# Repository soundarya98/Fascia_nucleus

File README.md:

# Fascia_nucleus
files related to the Fascia project

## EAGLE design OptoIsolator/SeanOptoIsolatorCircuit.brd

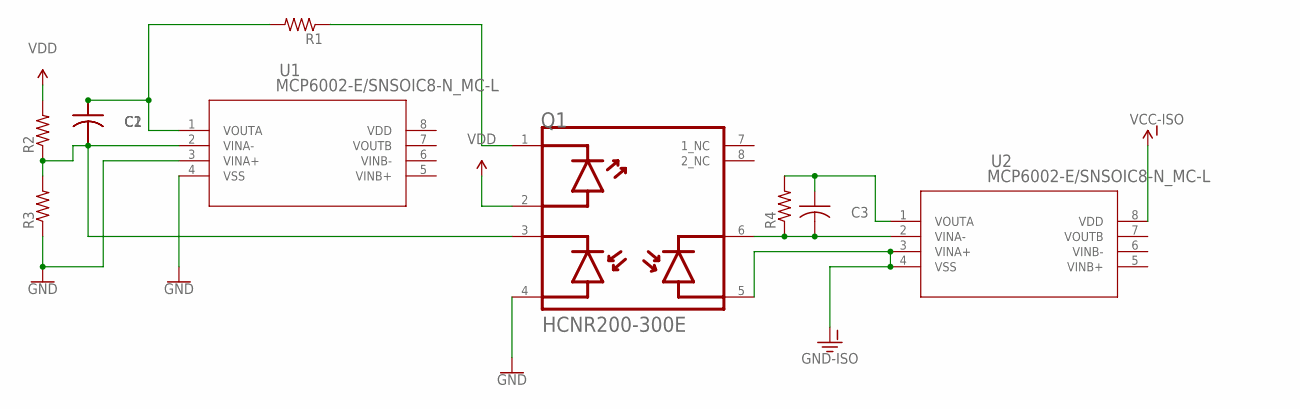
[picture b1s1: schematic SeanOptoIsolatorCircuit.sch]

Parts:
C1, C2, C3: C-US025-024X044; C025-024X044
Q1: BROADCOM_HCNR200-300EBROADCOM_HCNR200-300E_0_0; BROADCOM_HCNR200-300E_0
R1, R2, R3, R4: R-US_0204/5; 0204/5
U1, U2: MCP6002-E/SNSOIC8-N_MC-L; SOIC8-N_MC-L

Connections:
GND: Q1.4 (PD1_ANODE), R3.1, U1.3 (VINA+), U1.4 (VSS)
GND-ISO: Q1.5 (PD2_ANODE), U2.3 (VINA+), U2.4 (VSS)
unnamed: C1.2, C2.2, Q1.3 (PD1_CATHODE), R2.1, R3.2, U1.2 (VINA-)
unnamed: C1.1, C2.1, R1.2, U1.1 (VOUTA)
unnamed: Q1.1 (LED_CATHODE), R1.1
unnamed: C3.2, Q1.6 (PD2_CATHODE), R4.1, U2.2 (VINA-)
unnamed: C3.1, R4.2, U2.1 (VOUTA)
VCC-ISO: U2.8 (VDD)
VDD: Q1.2 (LED_ANODE), R2.2

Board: 2 copper layers, 10 parts (0 on the bottom side), 8 nets, no tracks yet.

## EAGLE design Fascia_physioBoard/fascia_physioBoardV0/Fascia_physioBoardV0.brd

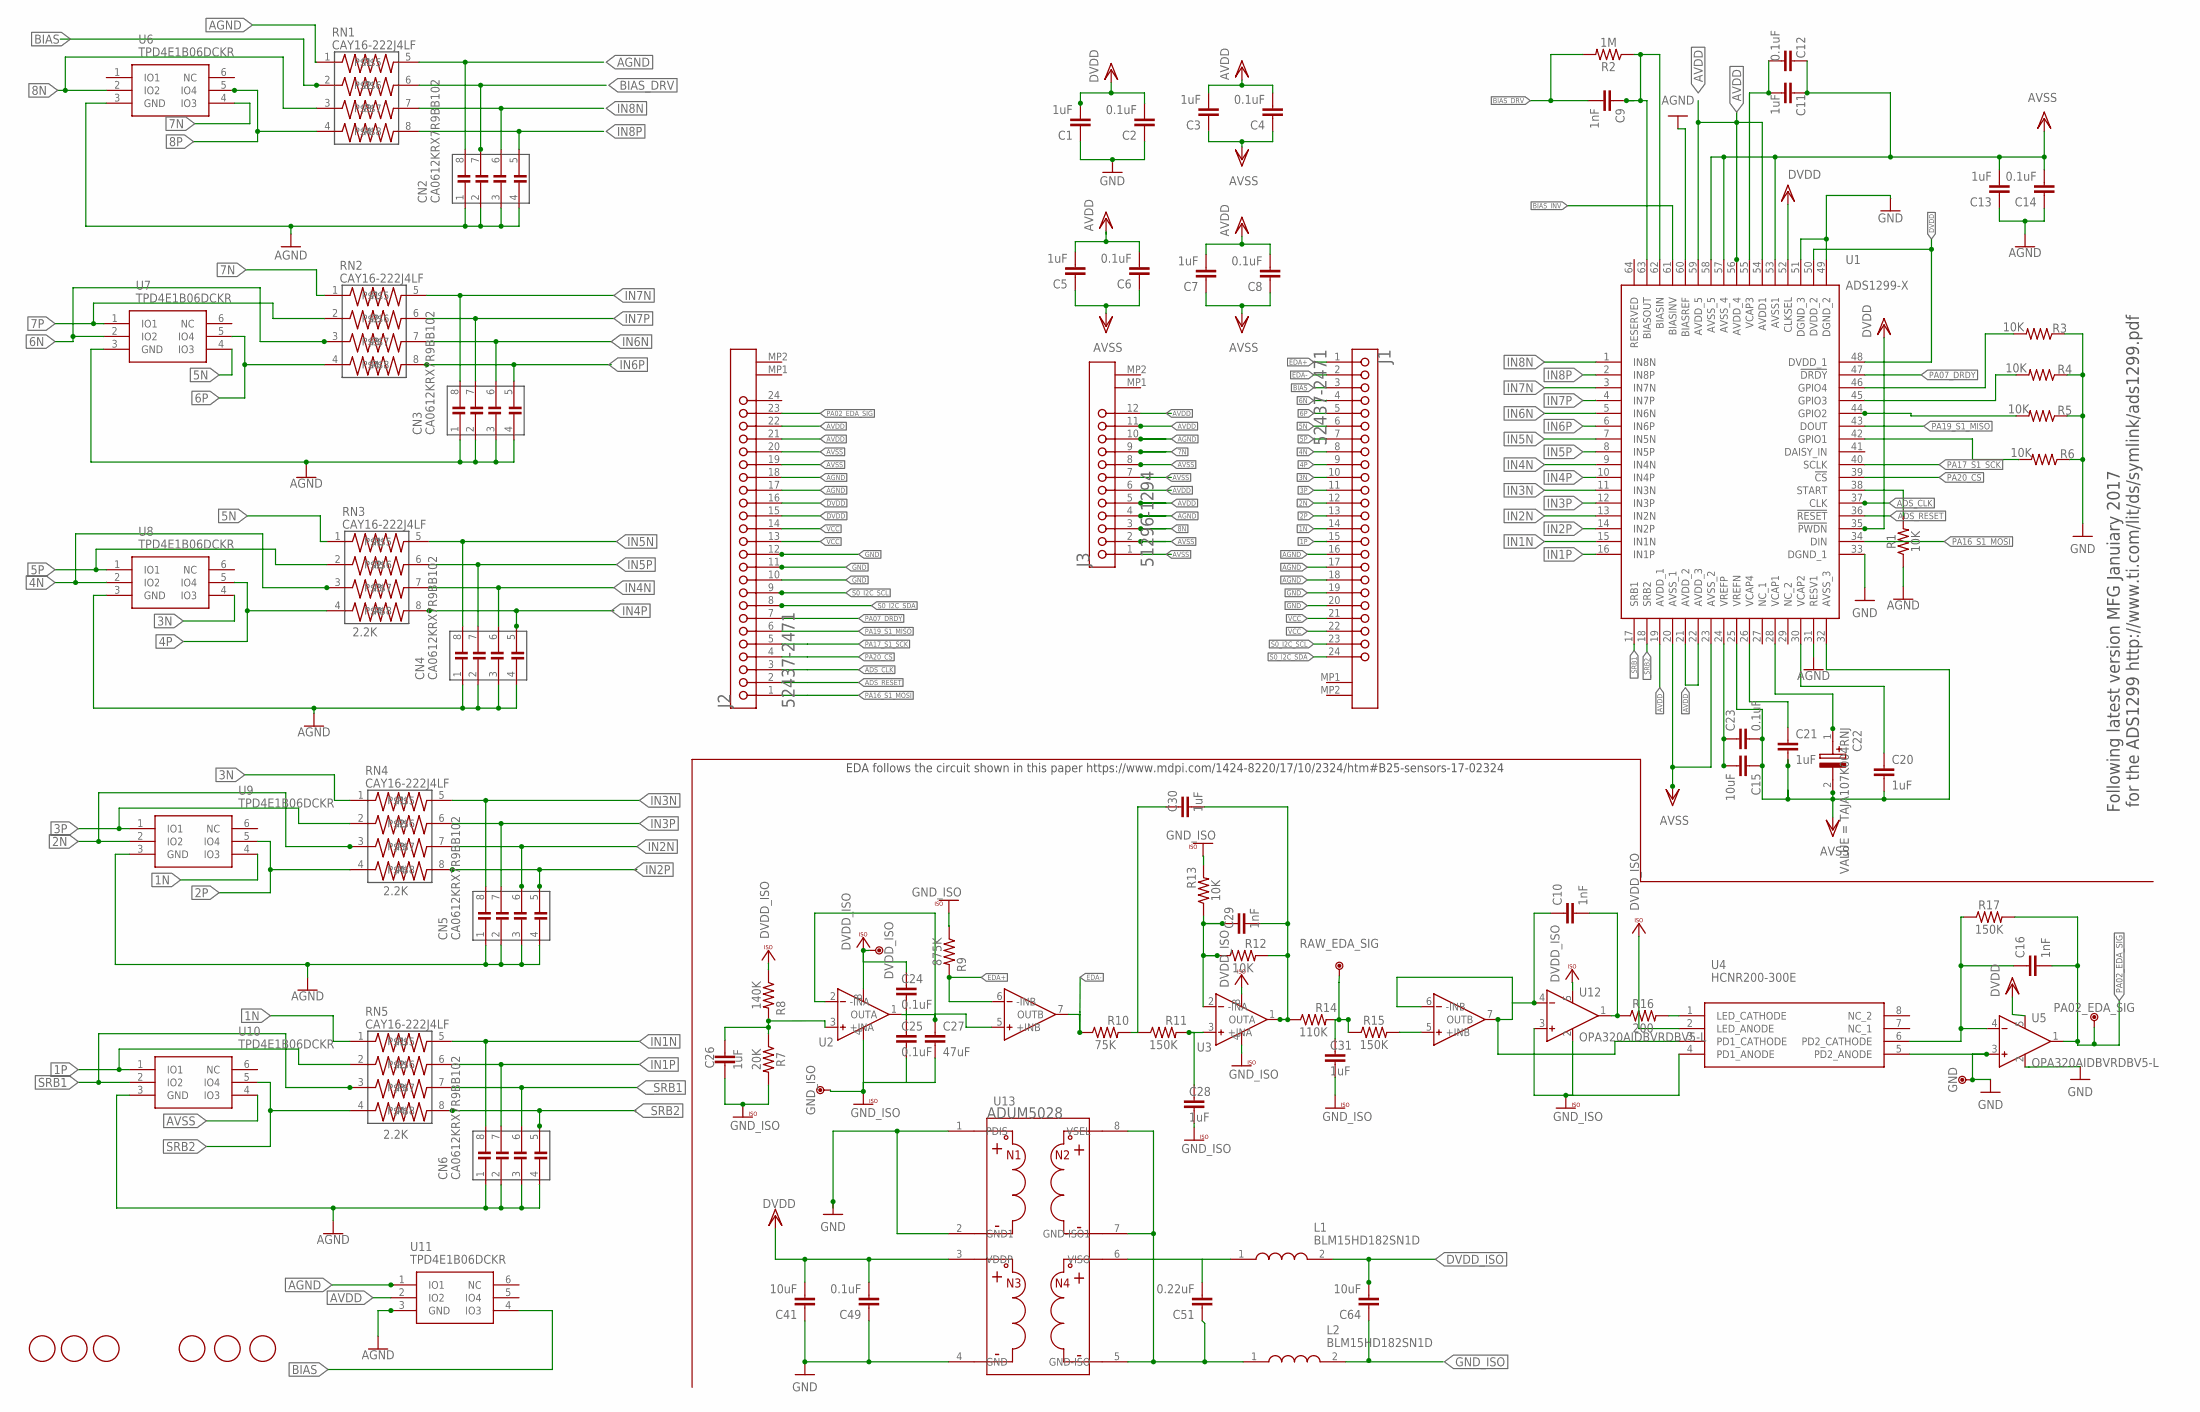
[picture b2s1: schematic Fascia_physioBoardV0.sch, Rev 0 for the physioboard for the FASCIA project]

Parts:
C1, C3, C5, C7, C11, C13, C20, C21, C26, C28, C30, C31: 1uF; 0402-TIGHT
C2, C4, C6, C8, C12, C14, C23, C24, C25, C49: 0.1uF; 0402-TIGHT
C9, C10, C16, C29: 1nF; 0402-TIGHT
C15: 10uF; 0402
C22: TAJA107K004RNJ; CAPPM3216X180N
C27: 47uF; 0603
C41, C64: 10uF; 0603
C51: 0.22uF; 0402-TIGHT
CN2, CN3, CN4, CN5, CN6: CA0612KRX7R9BB102
DVDD_ISO: DNP; TP-0.8MM
FD1, FD2, FD3, FD4, FD5, FD6: DNP; FD-1-1.5
GND: DNP; TP-0.8MM
GND_ISO: DNP; TP-0.8MM
J1, J2: MOLEX_52437-2471MOLEX_52437-2471_0_0; MOLEX_52437-2471_0
J3: MOLEX_51296-1294MOLEX_51296-1294_0_0; MOLEX_51296-1294_0
L1, L2: BLM15HD182SN1D; INDC1005X55N
PA02_EDA_SIG: DNP; TP-0.8MM
R1, R3, R4, R5, R6, R12, R13: 10K; 0402-TIGHT
R2: 1M; 0402-TIGHT
R7: 20K; 0402-TIGHT
R8: 140K; 0402-TIGHT
R9: 875K; 0402-TIGHT
R10: 75K; 0402-TIGHT
R11, R15, R17: 150K; 0402-TIGHT
R14: 110K; 0402-TIGHT
R16: 200; 0402-TIGHT
RAW_EDA_SIG: DNP; TP-0.8MM
RN1, RN2, RN3, RN4, RN5: CAY16-222J4LF
U1: ADS1299-X; QFP50P1200X1200X120-64N
U2: OPA2320AIDGKT_NOVA8-SOIC-L; D8-L
U3: OPA2320AIDGKT_NOVAL8-SOIC-L; D8-L
U4: HCNR200-300E; SOP254P1230X400-8N
U5, U12: OPA320AIDBVRDBV5-L; DBV5-L
U6, U7, U8, U9, U10, U11: TPD4E1B06DCKR; SOT65P210X110-6N
U13: ADUM5028; SOIC_IC

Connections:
1N: J1.14, RN5.1, U9.4 (IO3)
1P: J1.15, RN5.2, U10.1 (IO1)
2N: J1.12, RN4.3, U9.2 (IO2)
2P: J1.13, RN4.4, U9.5 (IO4)
3N: J1.10, RN4.1, U8.4 (IO3)
3P: J1.11, RN4.2, U9.1 (IO1)
4N: J1.8, RN3.3, U8.2 (IO2)
4P: J1.9, RN3.4, U8.5 (IO4)
5N: J1.6, RN3.1, U7.4 (IO3)
5P: J1.7, RN3.2, U8.1 (IO1)
6N: J1.4, RN2.3, U7.2 (IO2)
6P: J1.5, RN2.4, U7.5 (IO4)
7N: J3.9, RN2.1, U6.4 (IO3)
7P: RN2.2, U7.1 (IO1)
8N: J3.3, RN1.3, U6.2 (IO2)
8P: RN1.4, U6.5 (IO4)
ADS_CLK: J2.3, U1.37 (CLK)
ADS_RESET: J2.2, U1.36 (!RESET)
AGND: C13.1, C14.1, CN2.1 (C10), CN2.2 (C11), CN2.3 (C12), CN2.4 (C13), CN2.8 (C17), CN3.1 (C10), CN3.2 (C11), CN3.3 (C12), CN3.4 (C13), CN4.1 (C10), CN4.2 (C11), CN4.3 (C12), CN4.4 (C13), CN5.1 (C10), CN5.2 (C11), CN5.3 (C12), CN5.4 (C13), CN6.1 (C10), CN6.2 (C11), CN6.3 (C12), CN6.4 (C13), J1.16, J1.17, J1.18, J2.17, J2.18, J3.4, J3.10, R1.1, RN1.1, RN1.5, U1.31 (RESV1), U1.60 (BIASREF), U6.3 (GND), U7.3 (GND), U8.3 (GND), U9.3 (GND), U10.3 (GND), U11.1 (IO1), U11.3 (GND)
AVDD: C3.2, C4.2, C5.2, C6.2, C7.2, C8.2, J2.21, J2.22, J3.5, J3.6, J3.11, J3.12, U1.19 (AVDD_1), U1.21 (AVDD_2), U1.22 (AVDD_3), U1.54 (AVDD1), U1.56 (AVDD_4), U1.59 (AVDD_5), U11.2 (IO2)
AVSS: C3.1, C4.1, C5.1, C6.1, C7.1, C8.1, C11.1, C12.1, C13.2, C14.2, C15.1, C20.2, C21.2, C22.2 (-), C23.2, J2.19, J2.20, J3.1, J3.2, J3.7, J3.8, U1.20 (AVSS_1), U1.23 (AVSS_2), U1.25 (VREFN), U1.32 (AVSS_3), U1.53 (AVSS1), U1.57 (AVSS_4), U1.58 (AVSS_5), U10.4 (IO3)
BIAS: J1.3, RN1.2, U11.4 (IO3)
BIAS_DRV: C9.2, CN2.7 (C16), R2.2, RN1.6
BIAS_INV: U1.61 (BIASINV)
DVDD: C1.2, C2.2, C41.2, C49.2, J2.15, J2.16, U1.35 (!PWDN), U1.48 (DVDD_1), U1.50 (DVDD_2), U1.52 (CLKSEL), U5.5 (V+), U13.3 (VDDP)
DVDD_ISO: C24.1, C64.2, DVDD_ISO.X, L1.2, R8.1, U2.8 (V+), U3.8 (V+), U4.2 (LED_ANODE), U12.5 (V+)
EDA+: J1.1, R9.2, U2.6 (-INB)
EDA-: J1.2, R10.1, U2.7 (OUTB)
GND: C1.1, C2.1, C41.1, C49.1, GND.X, J1.19, J1.20, J2.10, J2.11, J2.12, R3.1, R4.1, R5.1, R6.1, U1.33 (DGND_1), U1.49 (DGND_2), U1.51 (DGND_3), U4.5 (PD2_ANODE), U5.2 (V-), U5.3 (IN+), U13.1 (PDIS), U13.2 (GND1), U13.4 (GND)
GND_ISO: C25.2, C26.2, C27.2, C28.2, C31.2, C51.1, C64.1, GND_ISO.X, L2.1, L2.2, R7.2, R9.1, R13.2, U2.4 (V-), U3.4 (V-), U4.4 (PD1_ANODE), U12.2 (V-), U12.3 (IN+), U13.5 (GND-ISO), U13.7 (GND-ISO1), U13.8 (VSEL)
IN1N: CN6.8 (C17), RN5.5, U1.15 (IN1N)
IN1P: CN6.7 (C16), RN5.6, U1.16 (IN1P)
IN2N: CN5.6 (C15), RN4.7, U1.13 (IN2N)
IN2P: CN5.5 (C14), RN4.8, U1.14 (IN2P)
IN3N: CN5.8 (C17), RN4.5, U1.11 (IN3N)
IN3P: CN5.7 (C16), RN4.6, U1.12 (IN3P)
IN4N: CN4.6 (C15), RN3.7, U1.9 (IN4N)
IN4P: CN4.5 (C14), RN3.8, U1.10 (IN4P)
IN5N: CN4.8 (C17), RN3.5, U1.7 (IN5N)
IN5P: CN4.7 (C16), RN3.6, U1.8 (IN5P)
IN6N: CN3.6 (C15), RN2.7, U1.5 (IN6N)
IN6P: CN3.5 (C14), RN2.8, U1.6 (IN6P)
IN7N: CN3.8 (C17), RN2.5, U1.3 (IN7N)
IN7P: CN3.7 (C16), RN2.6, U1.4 (IN7P)
IN8N: CN2.6 (C15), RN1.7, U1.1 (IN8N)
IN8P: CN2.5 (C14), RN1.8, U1.2 (IN8P)
unnamed: C30.1, R10.2, R11.1
unnamed: C26.1, R7.1, R8.2, U2.3 (+INA)
unnamed: C28.1, R11.2, U3.3 (+INA)
unnamed: C31.1, R14.2, R15.1, RAW_EDA_SIG.X
unnamed: C10.2, R16.1, U12.1 (OUT)
unnamed: C51.2, L1.1, U13.6 (VISO)
unnamed: R16.2, U4.1 (LED_CATHODE)
unnamed: C16.1, R17.1, U4.6 (PD2_CATHODE), U5.4 (IN-)
unnamed: C29.1, R12.1, R13.1, U3.2 (-INA)
unnamed: C29.2, C30.2, R12.2, R14.1, U3.1 (OUTA)
unnamed: C24.2, C25.1, C27.1, U2.2 (-INA), U2.5 (+INB)
unnamed: R15.2, U3.5 (+INB)
unnamed: C10.1, U3.6 (-INB), U3.7 (OUTB), U4.3 (PD1_CATHODE), U12.4 (IN-)
unnamed: C9.1, R2.1, U1.62 (BIASIN), U1.63 (BIASOUT)
unnamed: C15.2, C23.1, U1.24 (VREFP)
unnamed: R3.2, U1.46 (GPIO4)
unnamed: R4.2, U1.45 (GPIO3)
unnamed: R5.2, U1.44 (GPIO2)
unnamed: R6.2, U1.42 (GPIO1)
unnamed: C21.1, U1.26 (VCAP4)
unnamed: C22.1 (+), U1.28 (VCAP1)
unnamed: C20.1, U1.30 (VCAP2)
unnamed: C11.2, C12.2, U1.55 (VCAP3)
unnamed: R1.2, U1.38 (START)
PA02_EDA_SIG: C16.2, J2.23, PA02_EDA_SIG.X, R17.2, U5.1 (OUT)
PA07_DRDY: J2.7, U1.47 (!DRDY)
PA16_S1_MOSI: J2.1, U1.34 (DIN)
PA17_S1_SCK: J2.5, U1.40 (SCLK)
PA19_S1_MISO: J2.6, U1.43 (DOUT)
PA20_CS: J2.4, U1.39 (!CS)
S0_I2C_SCL: J1.23, J2.9
S0_I2C_SDA: J1.24, J2.8
SRB1: RN5.3, U10.2 (IO2)
SRB2: RN5.4, U10.5 (IO4)
VCC: J1.21, J1.22, J2.13, J2.14
_SRB1: CN6.6 (C15), RN5.7, U1.17 (SRB1)
_SRB2: CN6.5 (C14), RN5.8, U1.18 (SRB2)

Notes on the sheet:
2.2K
Following latest version MFG Januiary 2017 for the ADS1299 http://www.ti.com/lit/ds/symlink/ads1299.pdf
EDA follows the circuit shown in this paper https://www.mdpi.com/1424-8220/17/10/2324/htm#B25-sensors-17-02324
ADUM5028

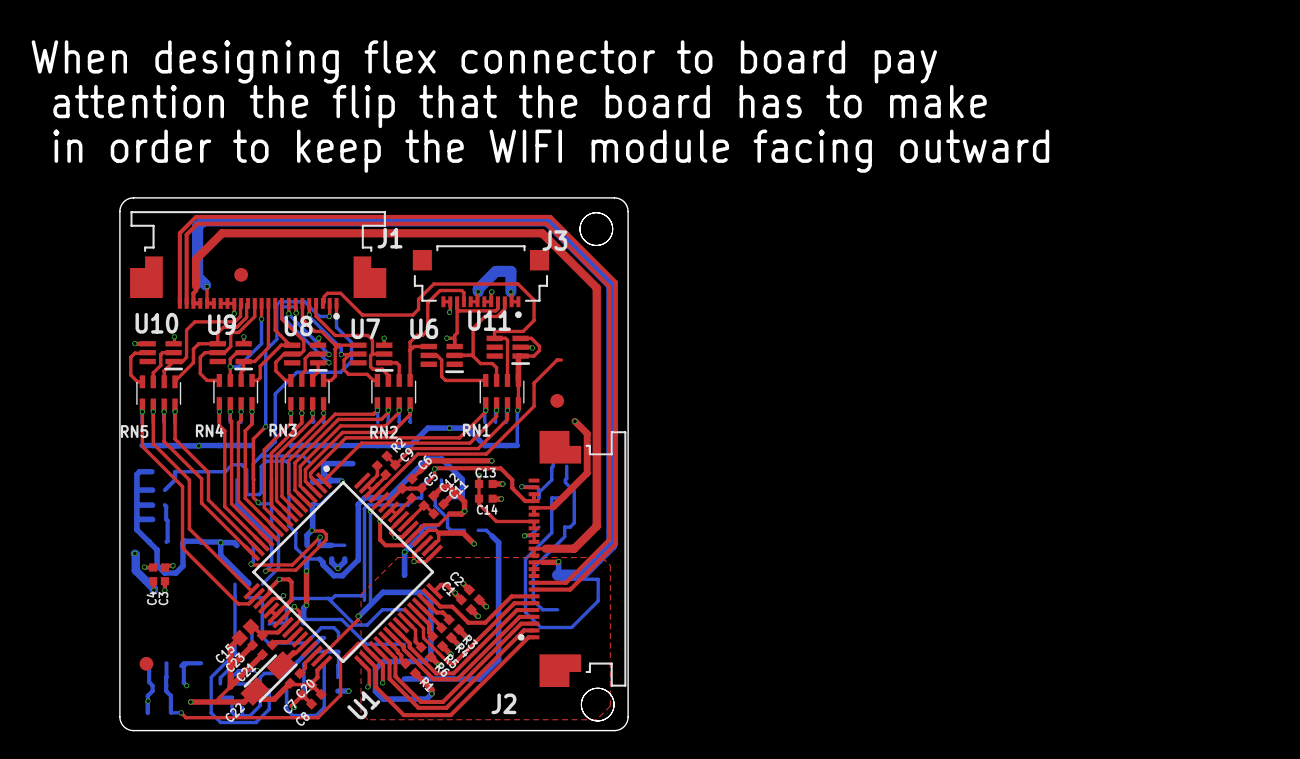
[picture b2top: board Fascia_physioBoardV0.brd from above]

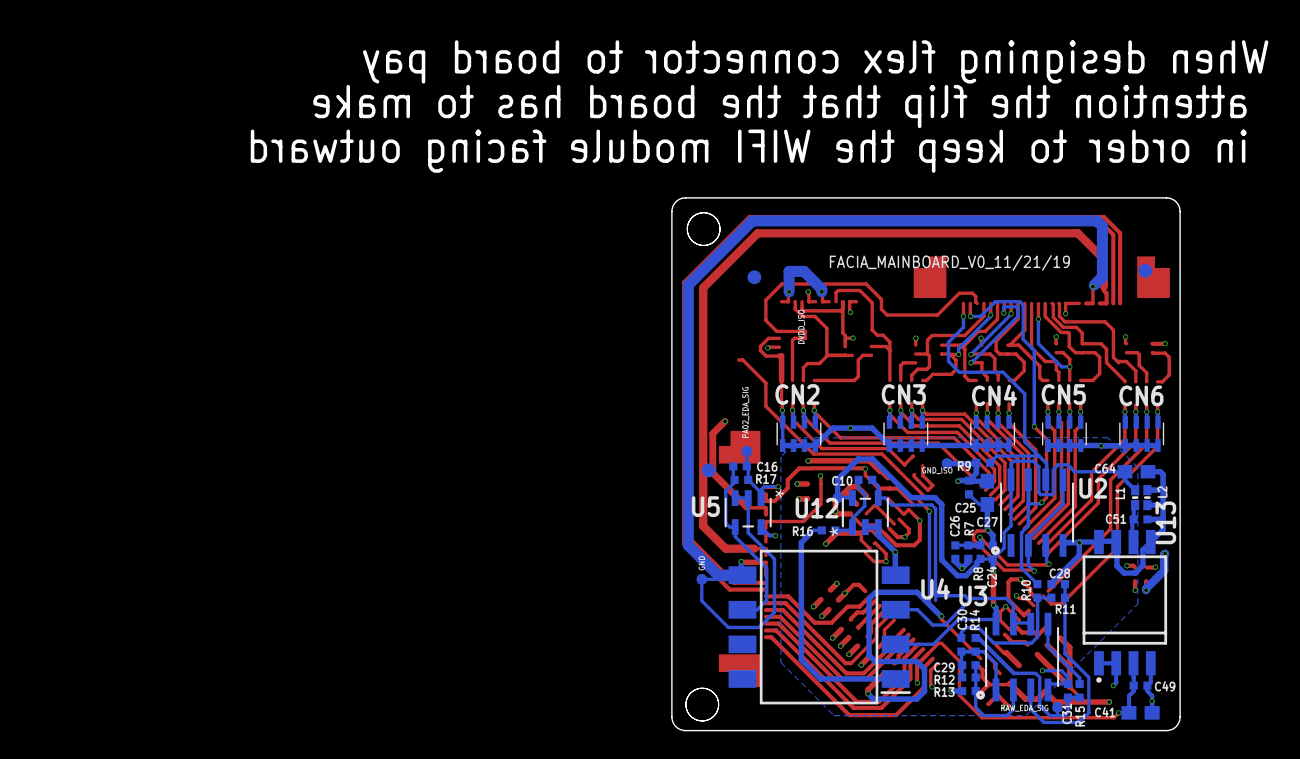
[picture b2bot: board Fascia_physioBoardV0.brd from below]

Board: 4 copper layers, 37.3 x 39.1 mm, 88 parts (41 on the bottom side), 82 nets.

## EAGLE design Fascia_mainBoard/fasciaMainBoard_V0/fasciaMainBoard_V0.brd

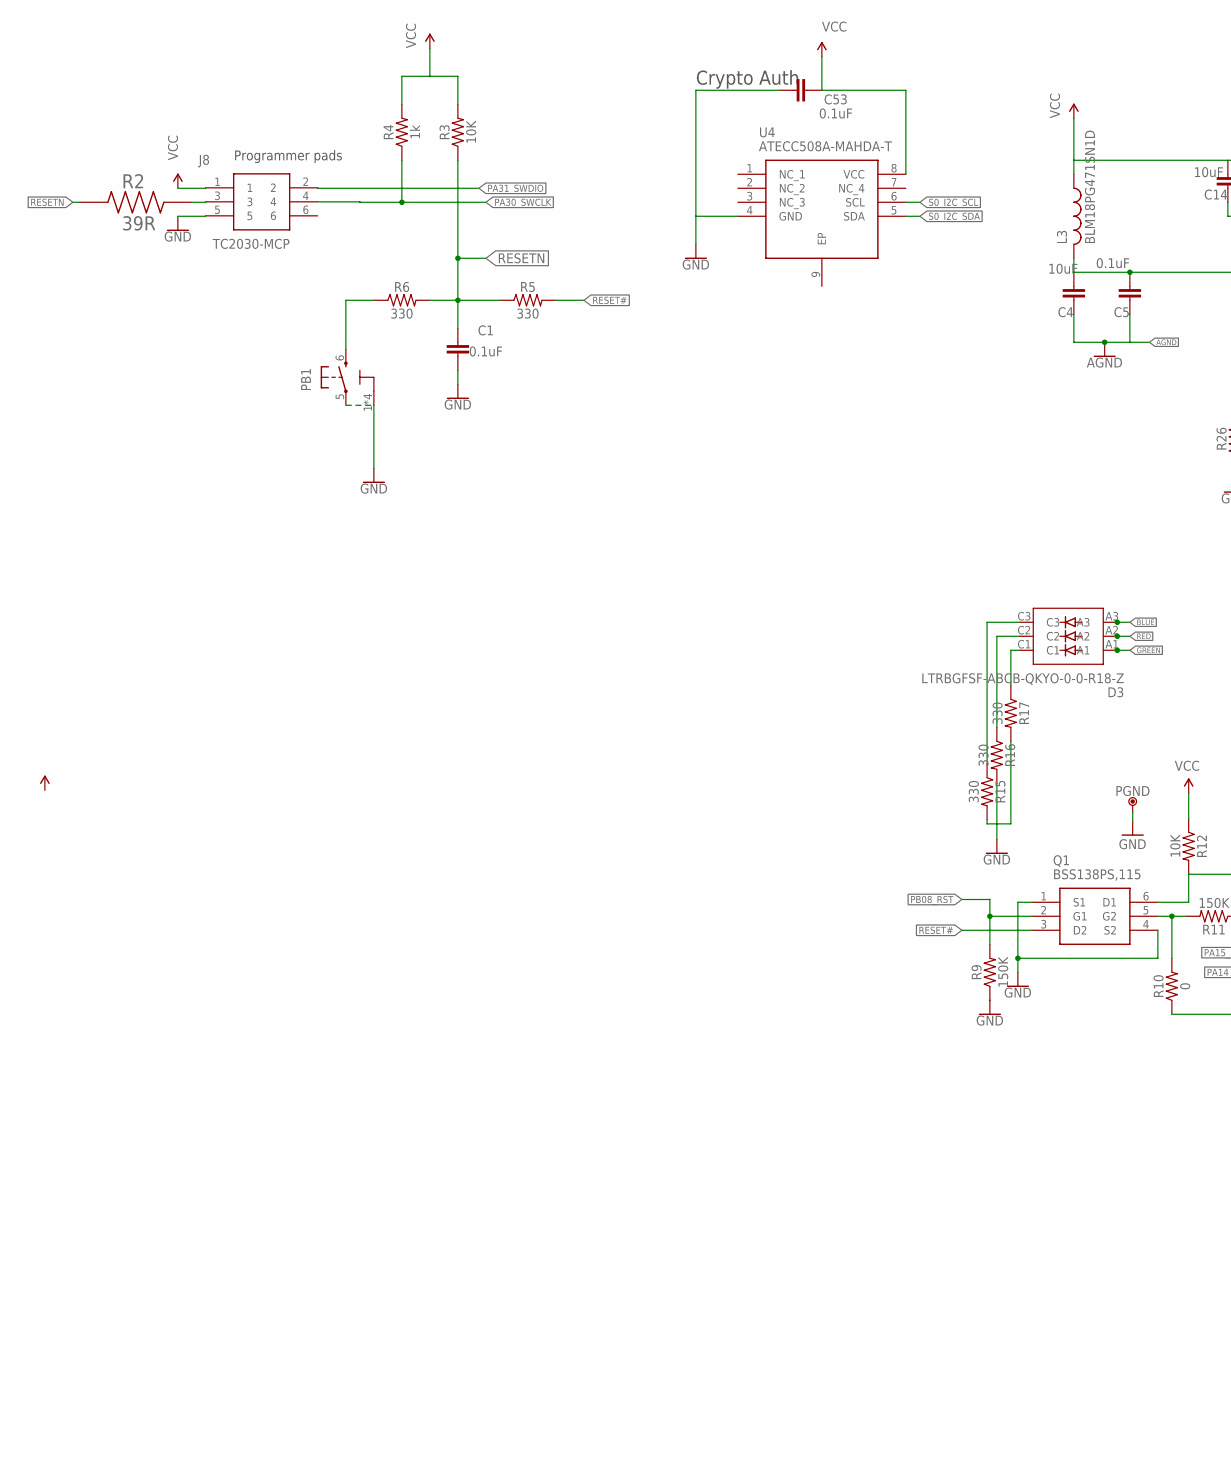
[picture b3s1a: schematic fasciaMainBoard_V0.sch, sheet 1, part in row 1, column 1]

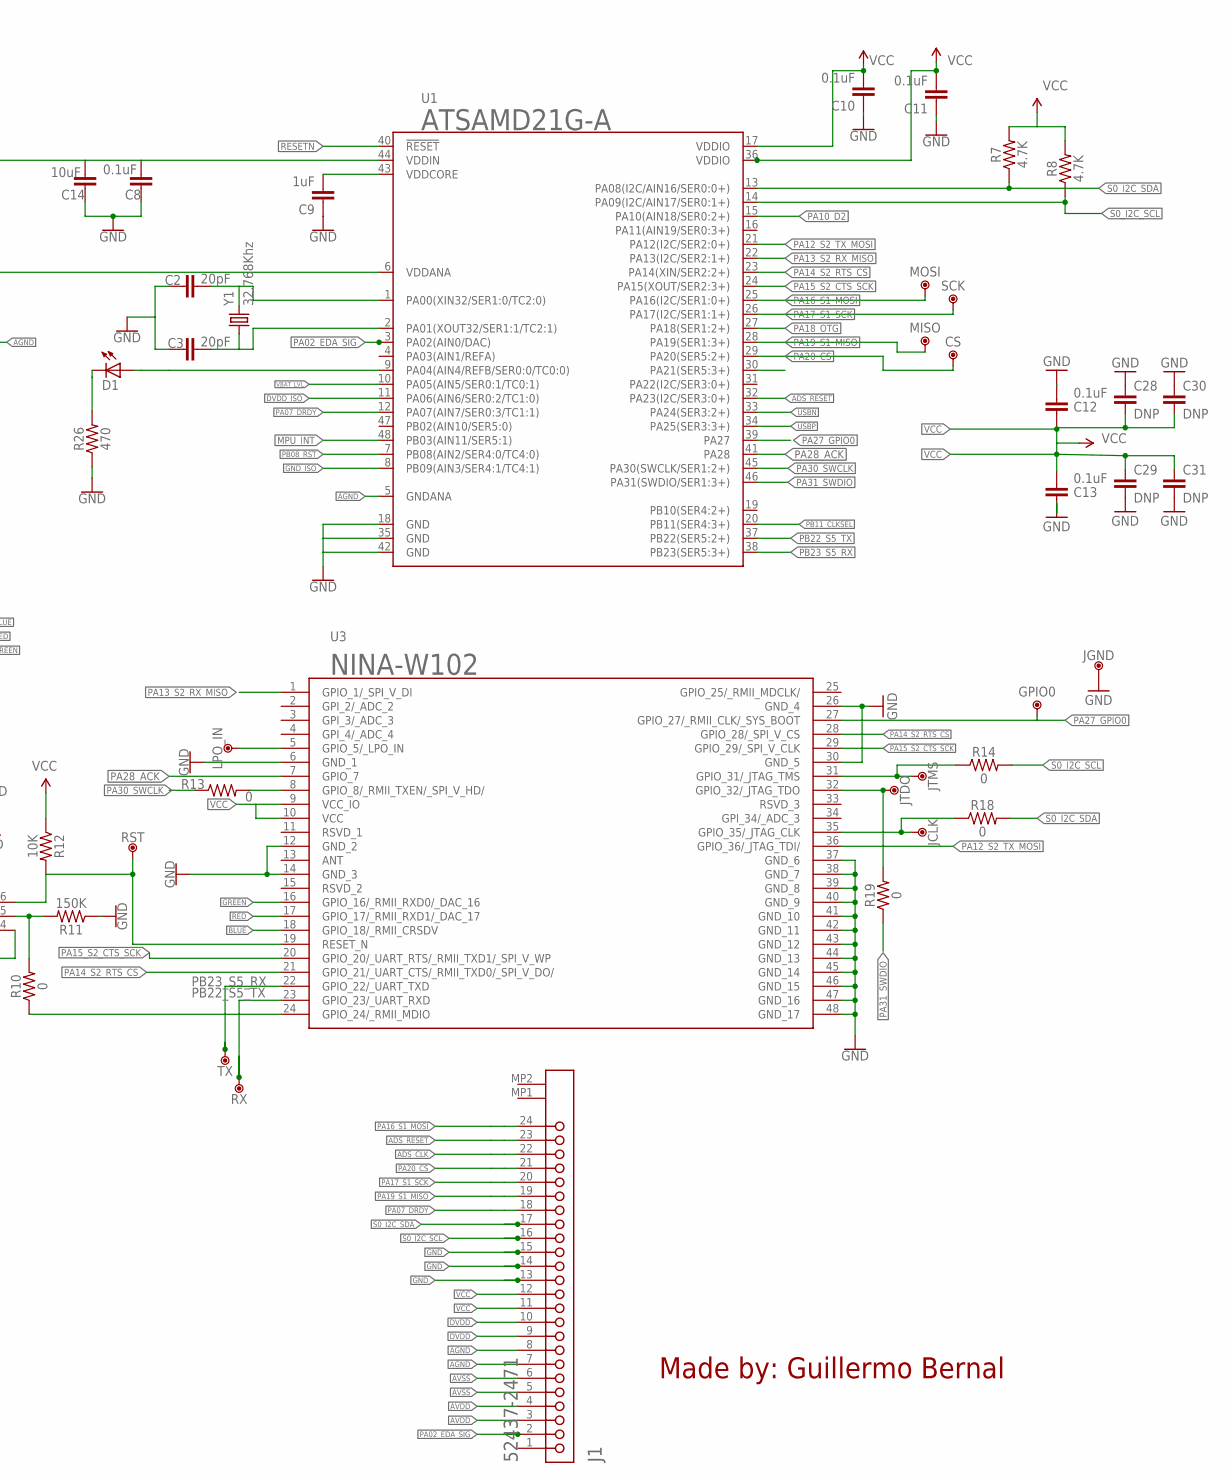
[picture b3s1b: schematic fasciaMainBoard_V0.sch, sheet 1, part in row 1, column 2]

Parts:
C1, C5, C8, C10, C11, C12, C13, C53: 0.1uF; 0402-TIGHT
C2, C3: 20pF; 0402-TIGHT
C4, C14: 10uF; 0603
C9: 1uF; 0402-TIGHT
C28, C29: DNP; 0402-1005X55N
C30, C31: DNP; 0603-1608X90N
CS: DNP; TP-0.8MM
D1: LEDCHIPLED_0603; CHIPLED_0603
D3: LTRBGFSF-ABCB-QKYO-0-0-R18-Z; PLCC-6
GPIO0: DNP; TP-0.8MM
J1: MOLEX_52437-2471MOLEX_52437-2471_0_0; MOLEX_52437-2471_0
J8: TC2030-MCP; TC2030MCP
JCLK: DNP; TP-0.8MM
JGND: DNP; TP-0.8MM
JTDO: DNP; TP-0.8MM
JTMS: DNP; TP-0.8MM
L3: BLM18PG471SN1D; BEADC1608X95N
LPO_IN: DNP; TP-0.8MM
MISO: DNP; TP-0.8MM
MOSI: DNP; TP-0.8MM
PB1: PTS820; C&K_PTS820_NO_HOLES
PGND: DNP; TP-0.8MM
Q1: BSS138PS,115; SOT65P210X110-6N
R2: 39R; RESC1005X40N
R3, R12: 10K; 0402-TIGHT
R4: 1k; 0402-TIGHT
R5, R6, R15, R16, R17: 330; 0402-TIGHT
R7, R8: 4.7K; 0402-TIGHT
R9, R11: 150K; 0402-TIGHT
R10, R13, R14, R18, R19: 0; 0402-TIGHT
R26: 470; 0402-TIGHT
RST: DNP; TP-0.8MM
RX: DNP; TP-0.8MM
SCK: DNP; TP-0.8MM
TX: DNP; TP-0.8MM
U1: ATSAMD21G-A; TQFP-48
U3: NINA-W102; NINAW102
U4: ATECC508A-MAHDA-T; SON50P300X200X60-9N
Y1: 32.768Khz; ECX-31B

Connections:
ADS_CLK: J1.22
ADS_RESET: J1.23, U1.32 (PA23(I2C/SER3:0+))
AGND: C4.1, C5.1, J1.7, J1.8, U1.5 (GNDANA); also elsewhere on the board
AVDD: J1.3, J1.4; also elsewhere on the board
AVSS: J1.5, J1.6; also elsewhere on the board
BLUE: D3.A3, U3.18 (GPIO_18/_RMII_CRSDV)
DVDD: J1.9, J1.10; also elsewhere on the board
DVDD_ISO: U1.11 (PA06(AIN6/SER0:2/TC1:0))
GND: C1.2, C2.1, C3.1, C8.1, C9.1, C10.1, C11.1, C12.2, C13.1, C14.1, C28.1, C29.2, C30.1, C31.2, C53.2, J1.13, J1.14, J1.15, J8.5, JGND.X, PB1.1 (3), PB1.2 (3), PB1.3, PB1.4 (3), PB1.5 (1), PGND.X, Q1.1 (S1), Q1.4 (S2), R9.1, R11.1, R15.2, R16.2, R17.2, R26.1, U1.18 (GND), U1.35 (GND), U1.42 (GND), U3.6 (GND_1), U3.12 (GND_2), U3.14 (GND_3), U3.26 (GND_4), U3.30 (GND_5), U3.37 (GND_6), U3.38 (GND_7), U3.39 (GND_8), U3.40 (GND_9), U3.41 (GND_10), U3.42 (GND_11), U3.43 (GND_12), U3.44 (GND_13), U3.45 (GND_14), U3.46 (GND_15), U3.47 (GND_16), U3.48 (GND_17), U4.4 (GND); also elsewhere on the board
GND_ISO: U1.8 (PB09(AIN3/SER4:1/TC4:1))
GREEN: D3.A1, U3.16 (GPIO_16/_RMII_RXD0/_DAC_16)
MPU_INT: U1.48 (PB03(AIN11/SER5:1)); also elsewhere on the board
unnamed: J8.3, R2.2
unnamed: PB1.6 (2), R6.1
unnamed: C2.2, U1.1 (PA00(XIN32/SER1:0/TC2:0)), Y1.2
unnamed: C3.2, U1.2 (PA01(XOUT32/SER1:1/TC2:1)), Y1.1
unnamed: Q1.5 (G2), R10.2, R11.2
unnamed: R10.1, U3.24 (GPIO_24/_RMII_MDIO)
unnamed: C9.2, U1.43 (VDDCORE)
unnamed: R13.2, U3.8 (GPIO_8/_RMII_TXEN/_SPI_V_HD/)
unnamed: Q1.6 (D1), R12.2, RST.X, U3.19 (RESET_N)
unnamed: D1.C, R26.2
unnamed: D1.A, U1.9 (PA04(AIN4/REFB/SER0:0/TC0:0))
unnamed: D3.C1, R17.1
unnamed: D3.C2, R16.1
unnamed: D3.C3, R15.1
unnamed: JTMS.X, R14.1, U3.31 (GPIO_31/_JTAG_TMS)
unnamed: JTDO.X, R19.2, U3.32 (GPIO_32/_JTAG_TDO)
unnamed: JCLK.X, R18.1, U3.35 (GPIO_35/_JTAG_CLK)
unnamed: LPO_IN.X, U3.5 (GPIO_5/_LPO_IN)
PA02_EDA_SIG: J1.2, U1.3 (PA02(AIN0/DAC))
PA07_DRDY: J1.18, U1.12 (PA07(AIN7/SER0:3/TC1:1))
PA10_D2: U1.15 (PA10(AIN18/SER0:2+))
PA12_S2_TX_MOSI: U1.21 (PA12(I2C/SER2:0+)), U3.36 (GPIO_36/_JTAG_TDI/)
PA13_S2_RX_MISO: U1.22 (PA13(I2C/SER2:1+)), U3.1 (GPIO_1/_SPI_V_DI)
PA14_S2_RTS_CS: U1.23 (PA14(XIN/SER2:2+)), U3.21 (GPIO_21/_UART_CTS/_RMII_TXD0/_SPI_V_DO/), U3.28 (GPIO_28/_SPI_V_CS)
PA15_S2_CTS_SCK: U1.24 (PA15(XOUT/SER2:3+)), U3.20 (GPIO_20/_UART_RTS/_RMII_TXD1/_SPI_V_WP), U3.29 (GPIO_29/_SPI_V_CLK)
PA16_S1_MOSI: J1.24, MOSI.X, U1.25 (PA16(I2C/SER1:0+))
PA17_S1_SCK: J1.20, SCK.X, U1.26 (PA17(I2C/SER1:1+))
PA18_OTG: U1.27 (PA18(SER1:2+)); also elsewhere on the board
PA19_S1_MISO: J1.19, MISO.X, U1.28 (PA19(SER1:3+))
PA20_CS: CS.X, J1.21, U1.29 (PA20(SER5:2+))
PA21_CS1: U1.30 (PA21(SER5:3+))
PA27_GPIO0: GPIO0.X, U1.39 (PA27), U3.27 (GPIO_27/_RMII_CLK/_SYS_BOOT)
PA28_ACK: U1.41 (PA28), U3.7 (GPIO_7)
PA30_SWCLK: J8.4, R4.1, R13.1, U1.45 (PA30(SWCLK/SER1:2+))
PA31_SWDIO: J8.2, R19.1, U1.46 (PA31(SWDIO/SER1:3+))
PB08_RST: Q1.2 (G1), R9.2, U1.7 (PB08(AIN2/SER4:0/TC4:0))
PB11_CLKSEL: U1.20 (PB11(SER4:3+))
PB22_S5_TX: RX.X, U1.37 (PB22(SER5:2+)), U3.23 (GPIO_23/_UART_RXD)
PB23_S5_RX: TX.X, U1.38 (PB23(SER5:3+)), U3.22 (GPIO_22/_UART_TXD)
RED: D3.A2, U3.17 (GPIO_17/_RMII_RXD1/_DAC_17)
RESET#: Q1.3 (D2), R5.2
RESETN: C1.1, R2.1, R3.1, R5.1, R6.2, U1.40 (!RESET!)
S0_I2C_SCL: J1.16, R8.1, R14.2, U1.14 (PA09(I2C/AIN17/SER0:1+)), U4.6 (SCL); also elsewhere on the board
S0_I2C_SDA: J1.17, R7.1, R18.2, U1.13 (PA08(I2C/AIN16/SER0:0+)), U4.5 (SDA); also elsewhere on the board
USBN: U1.33 (PA24(SER3:2+)); also elsewhere on the board
USBP: U1.34 (PA25(SER3:3+)); also elsewhere on the board
VBAT_LVL: U1.10 (PA05(AIN5/SER0:1/TC0:1)); also elsewhere on the board
VCC: C8.2, C10.2, C11.2, C12.1, C13.2, C14.2, C28.2, C29.1, C30.2, C31.1, C53.1, J1.11, J1.12, J8.1, L3.1, R3.2, R4.2, R7.2, R8.2, R12.1, U1.17 (VDDIO), U1.36 (VDDIO), U1.44 (VDDIN), U3.9 (VCC_IO), U3.10 (VCC), U4.8 (VCC); also elsewhere on the board
VDDANA: C4.2, C5.2, L3.2, U1.6 (VDDANA)

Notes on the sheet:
Programmer pads
Crypto Auth
Made by: Guillermo Bernal

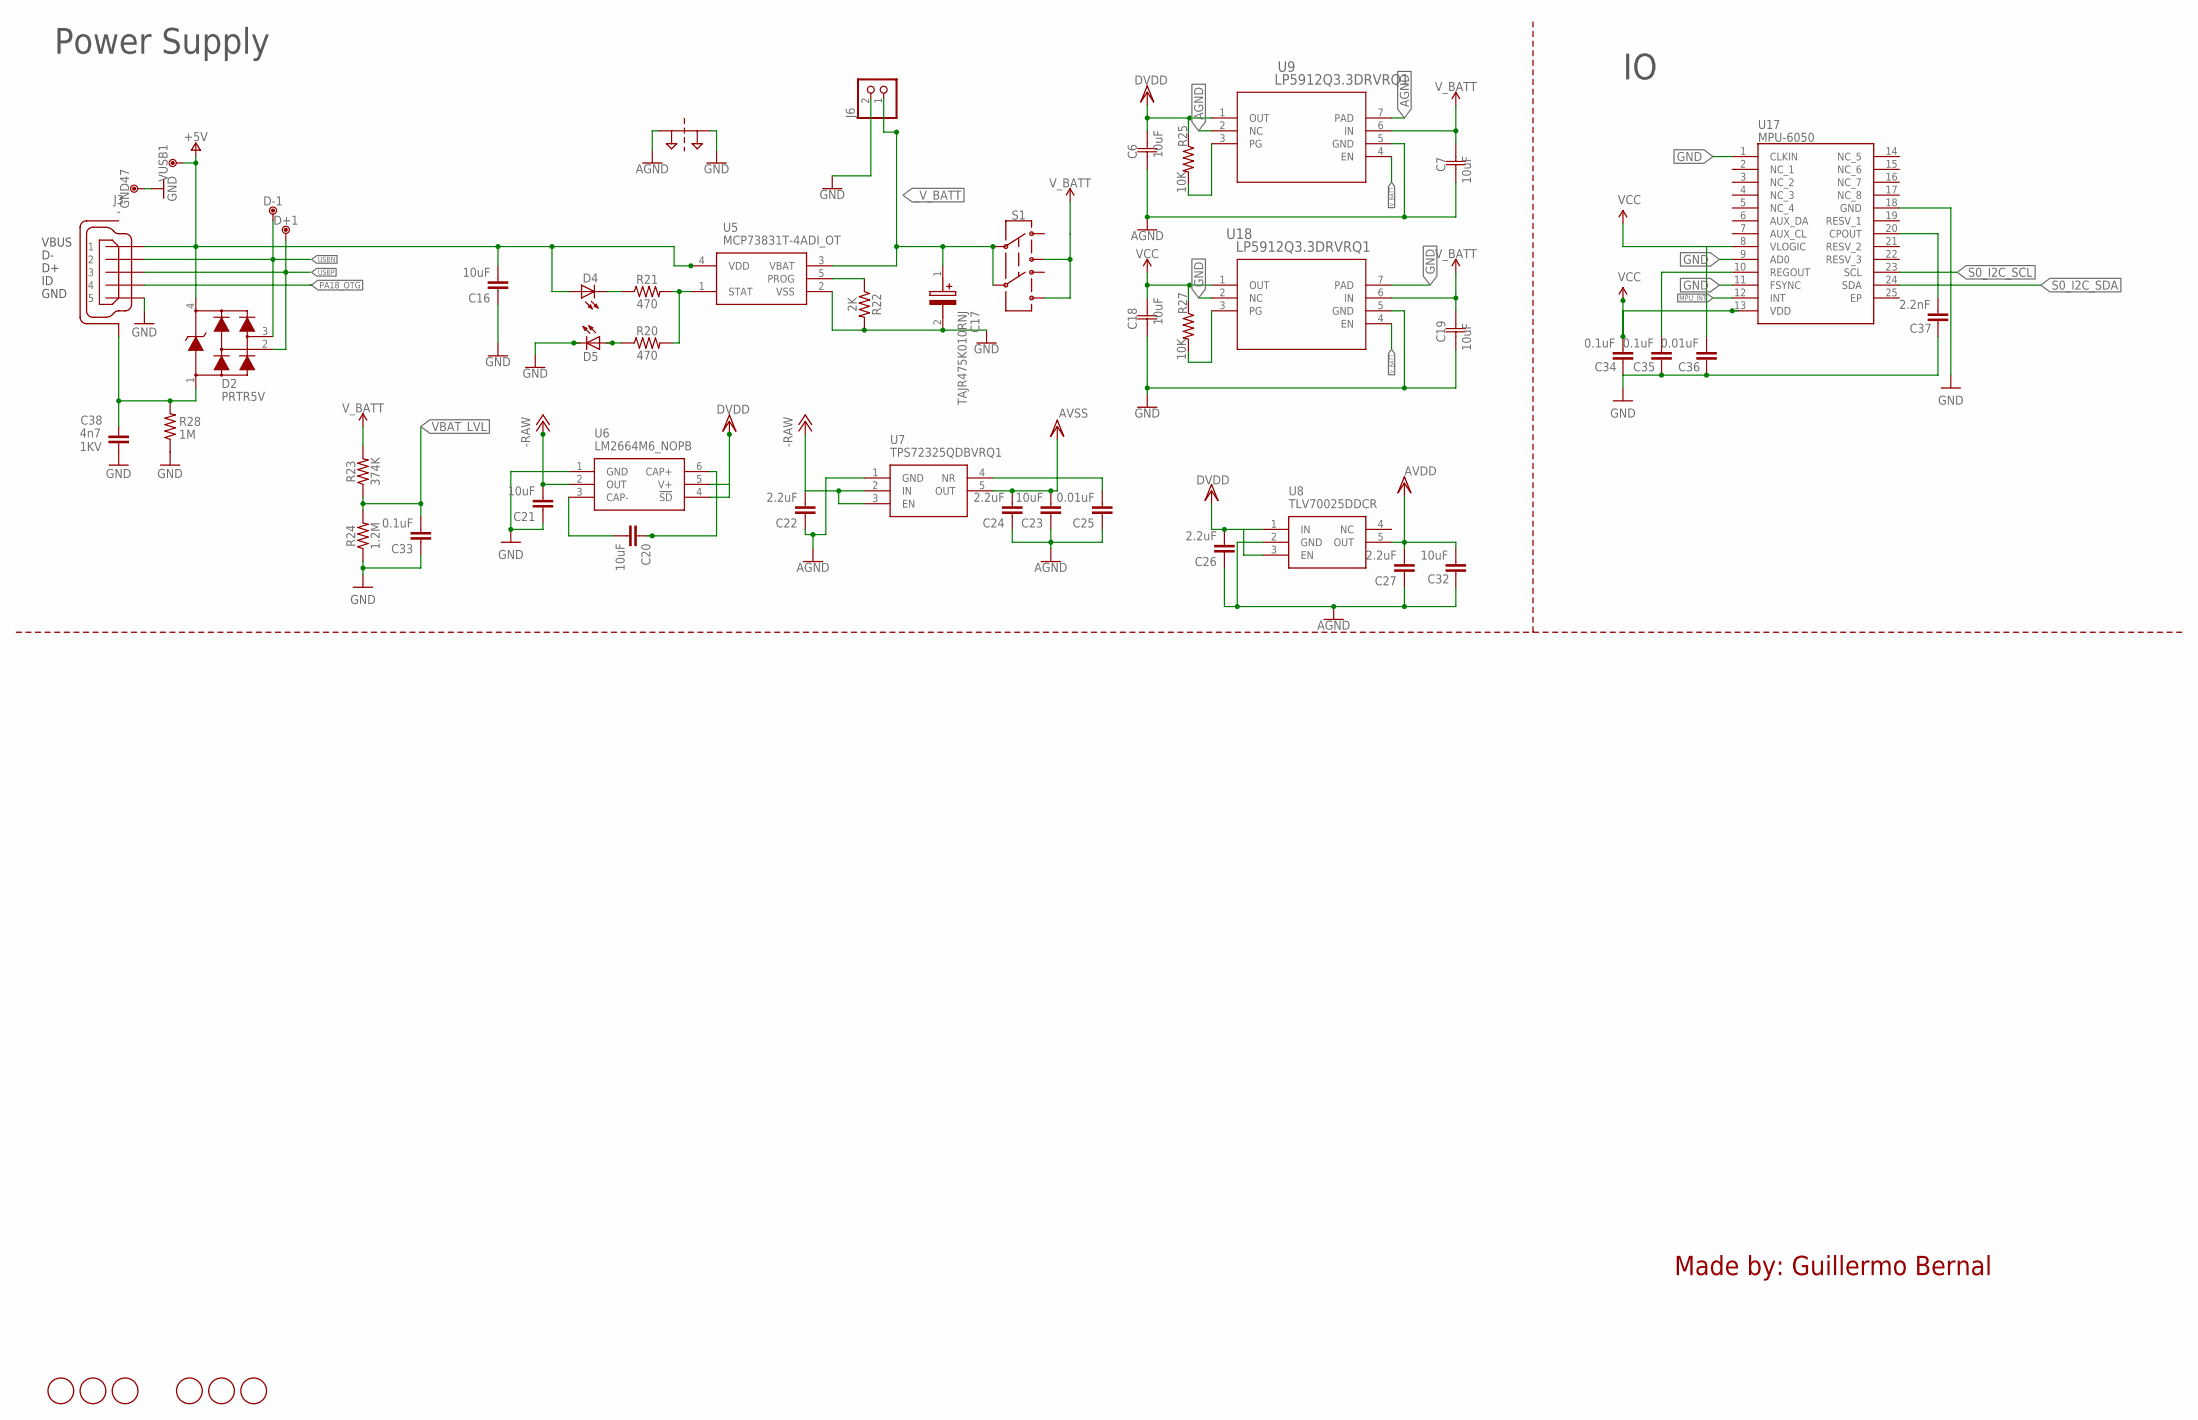
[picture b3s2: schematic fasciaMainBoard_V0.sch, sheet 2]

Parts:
C6, C7, C18, C19: 10uF; CAP_CL10-L
C16, C20, C21, C23, C32: 10uF; 0603
C17: TAJR475K010RNJ; CAPPM2014X120N
C22, C24, C26, C27: 2.2uF; 0402-TIGHT
C25, C36: 0.01uF; 0402-TIGHT
C33, C34, C35: 0.1uF; 0402-TIGHT
C37: 2.2nF; 0402-TIGHT
C38: 4n7; 0805-R2013X50N; VOLTAGE 1KV
D2: PRTR5V; SOT190P230X110-4N
D4, D5: LEDCHIPLED_0603; CHIPLED_0603
D+1: DNP; TP-1.00MM
D-1: DNP; TP-1.00MM
FD1, FD2, FD3, FD4, FD5, FD6: DNP; FD-1-1.5
GND47: DNP; TP-1.00MM
J3: -; ZX62-AB-5PA
J6: JST_2PIN-SMT-RA; JST-PH-2-SMT-RA
R20, R21: 470; 0402-TIGHT
R22: 2K; 0402-TIGHT
R23: 374K; 0402-TIGHT
R24: 1.2M; 0402
R25, R27: 10K; 0402-TIGHT
R28: 1M; 0402-TIGHT
S1: SWITCH-DPDT-SMD-AYZ0202; SWITCH_DPDT_SMD_AYZ0202
SUPPLY1: 2PT_GND_TIE
U5: MCP73831T-4ADI_OT; SOT95P270X145-5N
U6: LM2664M6_NOPB; SOT95P280X145-6N
U7: TPS72325QDBVRQ1; SOT96P230X110-5N
U8: TLV70025DDCR; SOT95P280X110-5N
U9, U18: LP5912Q3.3DRVRQ1; DRV0006A
U17: MPU-6050; MPU6050
VUSB1: DNP; TP-1.00MM

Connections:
+5V: C16.2, D2.4, D4.A, J3.1, U5.4 (VDD), VUSB1.X
-RAW: C21.2, C22.2, U6.2 (OUT), U7.2 (IN), U7.3 (EN)
AGND: C6.1, C7.1, C22.1, C23.1, C24.1, C25.1, C26.1, C27.1, C32.1, SUPPLY1.P$1, U7.1 (GND), U8.2 (GND), U9.2 (NC), U9.5 (GND), U9.7 (PAD); also elsewhere on the board
AVDD: C27.2, C32.2, U8.5 (OUT); also elsewhere on the board
AVSS: C23.2, C24.2, U7.5 (OUT); also elsewhere on the board
DVDD: C6.2, C26.2, R25.1, U6.4 (!SD), U6.5 (V+), U8.1 (IN), U8.3 (EN), U9.1 (OUT); also elsewhere on the board
GND: C16.1, C17.2 (-), C18.1, C19.1, C21.1, C33.1, C34.1, C35.1, C36.1, C37.1, C38.2, D5.C, GND47.X, J3.5, J6.2 (1), R22.2, R24.1, R28.1, SUPPLY1.P$2, U5.2 (VSS), U6.1 (GND), U17.1 (CLKIN), U17.9 (AD0), U17.11 (FSYNC), U17.18 (GND), U18.2 (NC), U18.5 (GND), U18.7 (PAD); also elsewhere on the board
MPU_INT: U17.12 (INT); also elsewhere on the board
unnamed: R27.2, U18.3 (PG)
unnamed: R25.2, U9.3 (PG)
unnamed: D4.C, R21.1
unnamed: R20.2, R21.2, U5.1 (STAT)
unnamed: R22.1, U5.5 (PROG)
unnamed: C20.2, U6.3 (CAP-)
unnamed: C20.1, U6.6 (CAP+)
unnamed: C25.2, U7.4 (NR)
unnamed: C35.2, U17.10 (REGOUT)
unnamed: C37.2, U17.20 (CPOUT)
unnamed: C38.1, D2.1, J3.6 (SH), J3.7 (SH), J3.8 (SH), J3.9 (SH), J3.10 (SH), J3.11 (SH), R28.2
unnamed: D5.A, R20.1
PA18_OTG: J3.4; also elsewhere on the board
S0_I2C_SCL: U17.23 (SCL); also elsewhere on the board
S0_I2C_SDA: U17.24 (SDA); also elsewhere on the board
USBN: D2.3, D-1.X, J3.2; also elsewhere on the board
USBP: D2.2, D+1.X, J3.3; also elsewhere on the board
VBAT_LVL: C33.2, R23.1, R24.2; also elsewhere on the board
VCC: C18.2, C34.2, C36.2, R27.1, U17.8 (VLOGIC), U17.13 (VDD), U18.1 (OUT); also elsewhere on the board
V_BATT: C7.2, C19.2, R23.2, S1.3, S1.6, U9.4 (EN), U9.6 (IN), U18.4 (EN), U18.6 (IN)
_V_BATT: C17.1 (+), J6.1 (2), S1.2, S1.5, U5.3 (VBAT)

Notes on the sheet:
Power Supply
Made by: Guillermo Bernal
374K

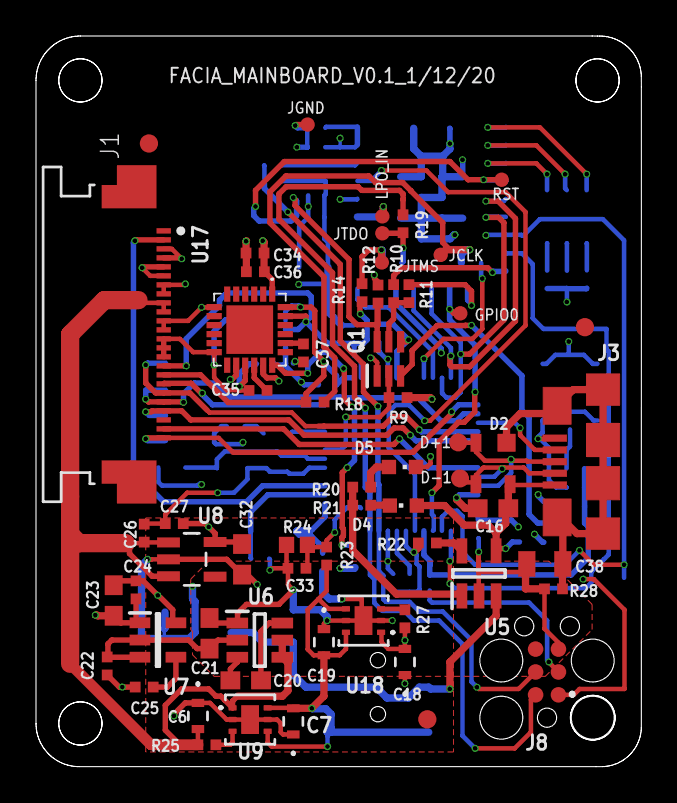
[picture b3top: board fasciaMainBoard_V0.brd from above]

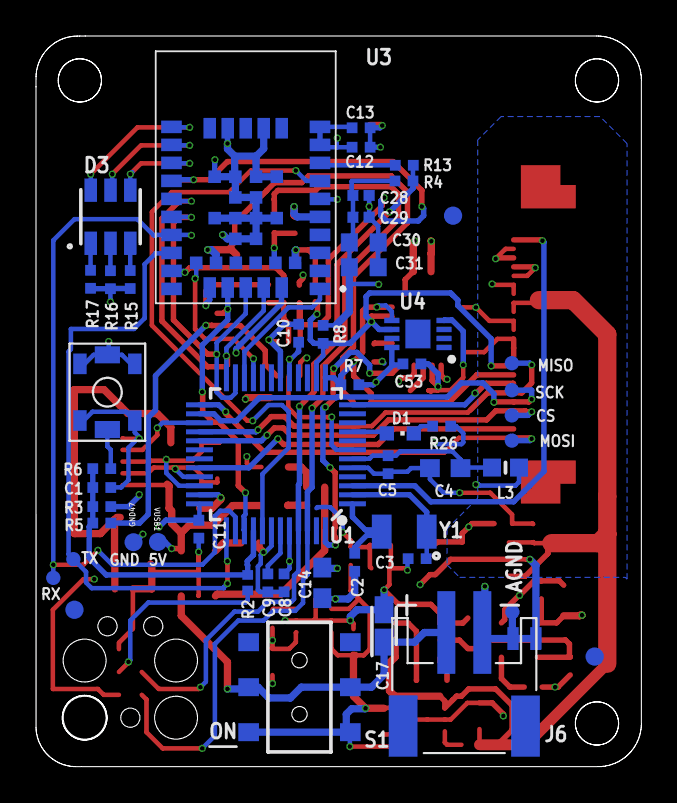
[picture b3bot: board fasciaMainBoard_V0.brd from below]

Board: 4 copper layers, 33.6 x 40.6 mm, 114 parts (53 on the bottom side), 71 nets.

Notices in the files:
parts and their libraries:
SparkFun-Connectors: Licensing: Creative Commons ShareAlike 4.0 International - https://creativecommons.org/licenses/by-sa/4.0
Arduino-connectors: Copyright (c) 2016-2017 Arduino LLC.  All right reserved.
COPYRIGHT: Copyright (C) 2018 Accelerated Designs. All rights reserved
